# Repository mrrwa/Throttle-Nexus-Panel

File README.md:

# Throttle Nexus Panel

This Eagle PCB CAD project provides an electrically neutral throttle connection panel that supports either the NCE Cab Bus or LocoNet, but not both at the same time.<br>

It provides 5 sockets all wired in parallel and adds some diagnostic LEDs to indicate:
- LocoNet RailSync presence indicated by the upper bi-colour Yellow/Green LED
- NCE Cable Bus Power status indicated by the lower bi-colour LED with RED for correct or "Good" polarity and Blue for reversed or "Bad" polarity.<br>

## Throttle Nexus Panel - Schematic

## Throttle Nexus Panel - PCB Board
A single PCB contains both the front panel with silkscreen lettering and a break-off PCB for mounting the RJ12 sockets and other components.<br>

This project is released under the Creative Commons Attribution ShareAlike 3.0 license (CC BY-SA 3.0)

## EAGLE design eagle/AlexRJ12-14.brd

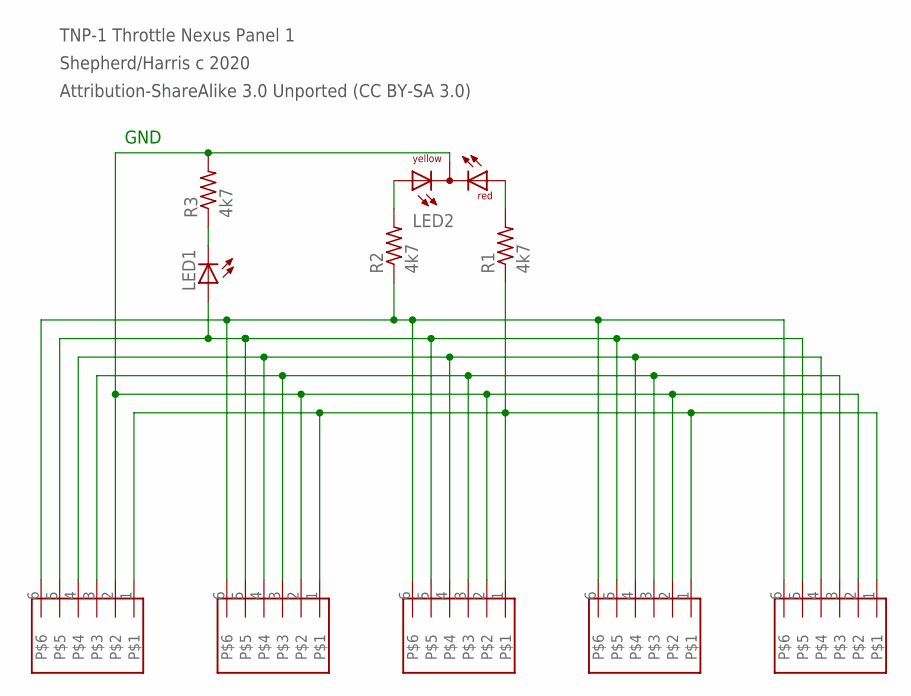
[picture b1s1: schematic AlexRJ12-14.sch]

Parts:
LED1: LED5MM
LED2: DUOLED-RY-C; DUOLED-C-5MM
R1, R2, R3: 4k7; 0207/7
U$1, U$2, U$3, U$4, U$5: RJ12-6

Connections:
L1: R1.1, U$1.1, U$2.1, U$3.1, U$4.1, U$5.1
L2: LED2.C, R3.2, U$1.2, U$2.2, U$3.2, U$4.2, U$5.2
L3: U$1.3, U$2.3, U$3.3, U$4.3, U$5.3
L4: U$1.4, U$2.4, U$3.4, U$4.4, U$5.4
L5: LED1.A, U$1.5, U$2.5, U$3.5, U$4.5, U$5.5
L6: R2.1, U$1.6, U$2.6, U$3.6, U$4.6, U$5.6
unnamed: LED2.AR, R1.2
unnamed: LED2.AX (AY), R2.2
unnamed: LED1.K (C), R3.1

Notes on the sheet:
GND
TNP-1 Throttle Nexus Panel 1
Shepherd/Harris c 2020
Attribution-ShareAlike 3.0 Unported (CC BY-SA 3.0)

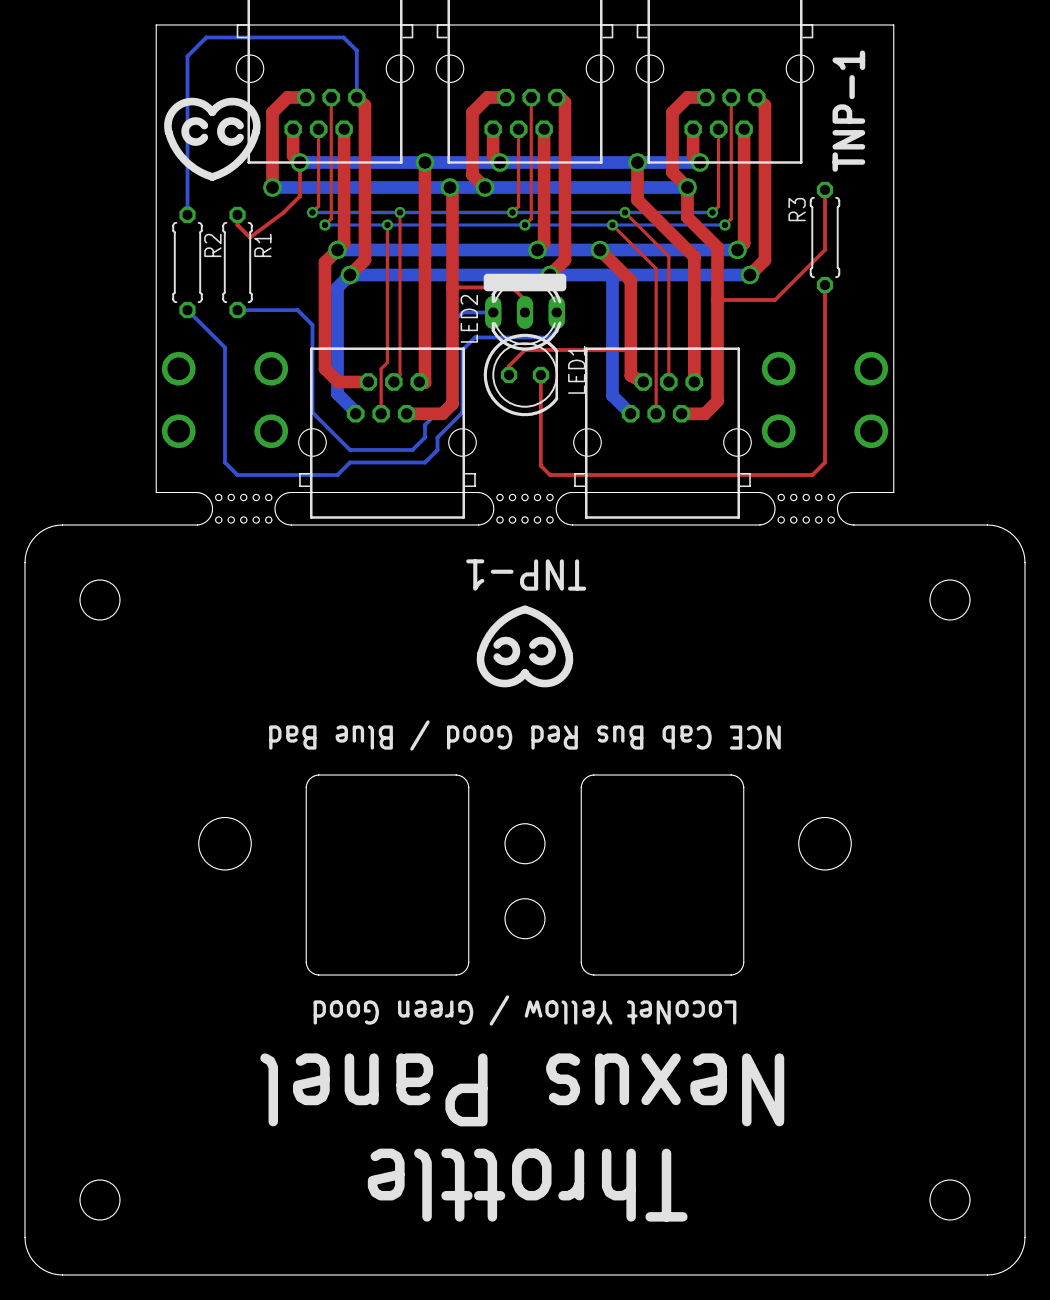
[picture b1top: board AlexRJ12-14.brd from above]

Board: 2 copper layers, 80.0 x 100.0 mm, 10 parts (0 on the bottom side), 9 nets.

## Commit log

2022-11-16 Added PNG files for as PDFs didn't display correctly
